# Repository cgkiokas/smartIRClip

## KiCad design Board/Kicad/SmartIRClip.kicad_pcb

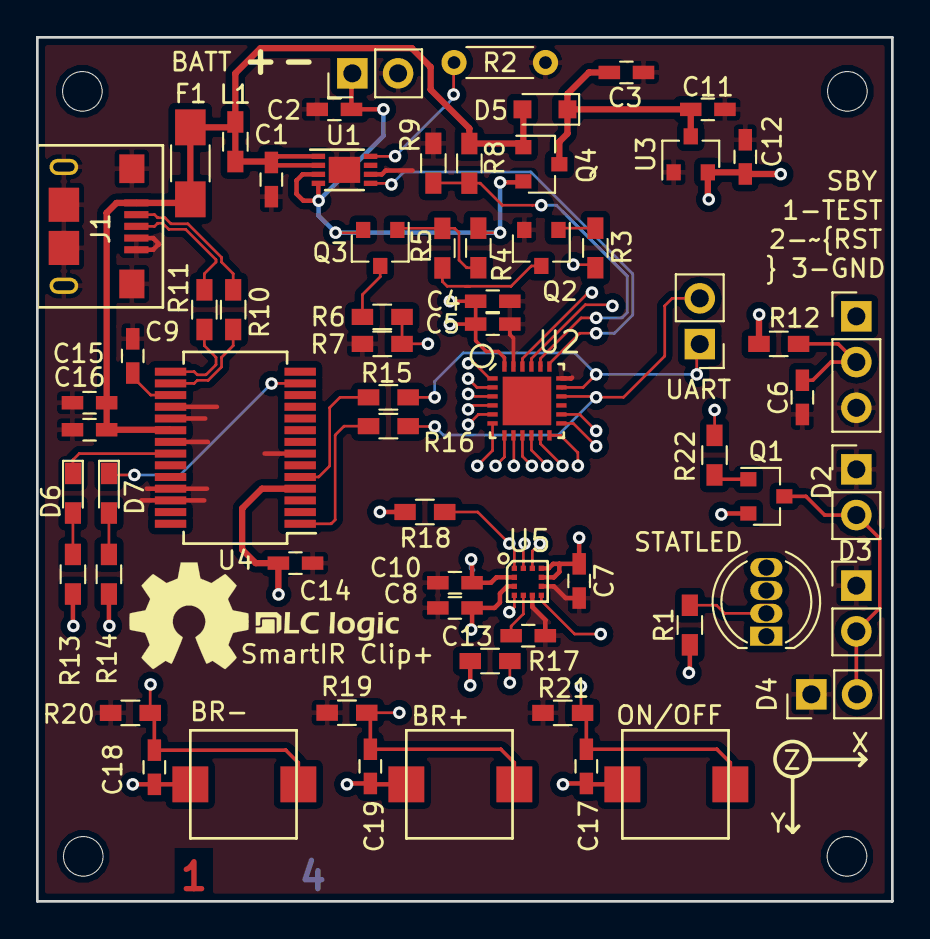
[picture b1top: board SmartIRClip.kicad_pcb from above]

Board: 4 copper layers, 47.5 x 48.0 mm, 66 parts (0 on the bottom side), 43 nets.

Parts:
BATT: Battery_Cell; Pin_Header_Straight_1x02_Pitch2.54mm
BR+: BRIGHT-; SKPSACE010
BR-: BRIGHT+; SKPSACE010
C1, C2: 4.7u; C_0603_HandSoldering
C3, C11, C12: 1u; C_0603_HandSoldering
C4, C7, C8, C9, C14, C16: 100n; C_0603_HandSoldering
C5, C10, C15: 10u; C_0603_HandSoldering
C6: 1n; C_0603_HandSoldering
C13: 220n; C_0603_HandSoldering
C17, C18, C19: 470n; C_0603_HandSoldering
D2, D3, D4: LED; Pin_Header_Straight_1x02_Pitch2.54mm
D5: D_Schottky; D_SOD-323_HandSoldering
D6, D7: LED; LED_0603_HandSoldering
F1: 16v/500Ma; R_1206_HandSoldering
J1: USB_OTG; FCI_10118193_0001LF
L1: 300m; L_0603_HandSoldering
ON/OFF: ON/OFF; SKPSACE010
Q1, Q4: DMP1045U; SOT-23
Q2: BC817-40; SOT-23
Q3: BC807-40; SOT-23
R1, R13, R14, R22: 20R; R_0603_HandSoldering
R2: 6250; R_Axial_DIN0204_L3.6mm_D1.6mm_P5.08mm_Horizontal
R3, R4, R5, R8, R9, R10, R11, R15, R16: 10k; R_0603_HandSoldering
R6: 7.5k; R_0603_HandSoldering
R7: 2.7k; R_0603_HandSoldering
R12, R19, R20, R21: 47k; R_0603_HandSoldering
R17, R18: 4.7k; R_0603_HandSoldering
SBY: SPYBYWIRE; Pin_Header_Straight_1x03_Pitch2.54mm
STATLED: LED_RAGB; LED_D5.0mm-4
U1: MCP73832; DFN-8-1EP_3x2mm_Pitch0.5mm
U2: MSP430FR2433
U3: MCP1700T; SOT-23
U4: FT232RL; SSOP-28_5.3x10.2mm_Pitch0.65mm
U5: LSM303AGRTR
UART: UART; Pin_Header_Straight_1x02_Pitch2.54mm

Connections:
+2V5: BR+.2, BR-.2, C4.2, C5.2, C7.1, C8.1, C10.1, C12.1, C14.2, C17.1, C18.1, C19.1, ON/OFF.2, Q1.2, R1.1, R12.2, R13.2, R14.2, R17.1, R18.1, U2.24, U3.2, U4.4, U5.2, U5.3, U5.9, U5.10
/BATTERY_SENSE: R6.2, R7.1, U2.8
/BATTERY_SENSE_EN: R3.1, U2.12
/BRIGHT+_SW: BR-.1, C18.2, R20.2, U2.22
/BRIGHT-_SW: BR+.1, C19.2, R19.2, U2.21
/CHARGE_STAT: U1.5, U2.19
/DISP_LED_B: STATLED.4, U2.5
/DISP_LED_G: STATLED.3, U2.3
/DISP_LED_R: STATLED.1, U2.4
/INT_1_XL: U2.11, U5.12
/INT_2_XL: U2.14, U5.11
/INT_MAG/DRDY: U2.13, U5.7
/IR_LED_CONTROL: R22.1, U2.7
/ON/OFF_SW: C17.2, ON/OFF.1, R21.2, U2.6
/SBWTDIO/RST: SBY.1, U2.2
/UART_RX: R16.1, U4.1
/UART_TX: R15.1, U4.5
/USB_D+: J1.3, R11.1, R11.2, U4.15
/USB_D-: J1.2, R10.1, R10.2, U4.16
/USB_IN_SENSE: R8.2, R9.1, U2.20
/USB_VCC: C1.1, C15.1, C16.1, D5.2, F1.1, F1.2, J1.1, L1.1, L1.2, Q4.1, R8.1, U1.1, U1.2, U4.20
/XL_SCL: R18.2, U2.10, U5.1
/XL_SDA: R17.2, U2.9, U5.4
GND: BATT.2, C1.2, C2.2, C3.2, C4.1, C5.1, C6.2, C7.2, C8.2, C9.2, C10.2, C11.2, C12.2, C13.2, C14.1, C15.2, C16.2, D2.1, D3.1, D4.1, J1.4, J1.5, J1.6, Q2.2, R2.2, R7.2, R9.2, R19.1, R20.1, R21.1, SBY.3, U1.6, U1.9, U2.18, U2.23, U3.1, U4.7, U4.18, U4.19, U4.21, U4.25, U4.26, U5.6, U5.8
unnamed: BATT.1, C2.1, Q3.2, Q4.2, R4.1, U1.3, U1.4
unnamed: C6.1, R12.1, SBY.2, U2.1
unnamed: C9.1, U4.17
unnamed: C13.1, U5.5
unnamed: R1.2, STATLED.2
unnamed: D2.2, D3.2, D4.2, Q1.3
unnamed: D6.1, U4.22
unnamed: D6.2, R13.1
unnamed: D7.1, U4.13
unnamed: D7.2, R14.1
unnamed: R15.2, U2.17, UART.1
unnamed: R16.2, U2.16, UART.2
unnamed: Q1.1, R22.2
unnamed: Q2.1, R3.2
unnamed: Q2.3, R5.2
unnamed: Q3.1, R4.2, R5.1
unnamed: Q3.3, R6.1
unnamed: R2.1, U1.8
VCC: C3.1, C11.1, D5.1, Q4.3, U3.3

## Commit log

2018-03-04 gitignore
2018-03-04 ignore
2018-03-04 cleanup
2018-03-04 more cleanup
2018-03-04 improvements
2018-03-04 layer counter
2018-03-04 project
2018-03-11 board send
